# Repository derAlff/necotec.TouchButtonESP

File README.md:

# touchButtonESP
DE: Ein klein wenig Code, zu meinem "Smarter Wandtaster Projekt". EN: A little bit of code, for my "smart wallmounted switch project".

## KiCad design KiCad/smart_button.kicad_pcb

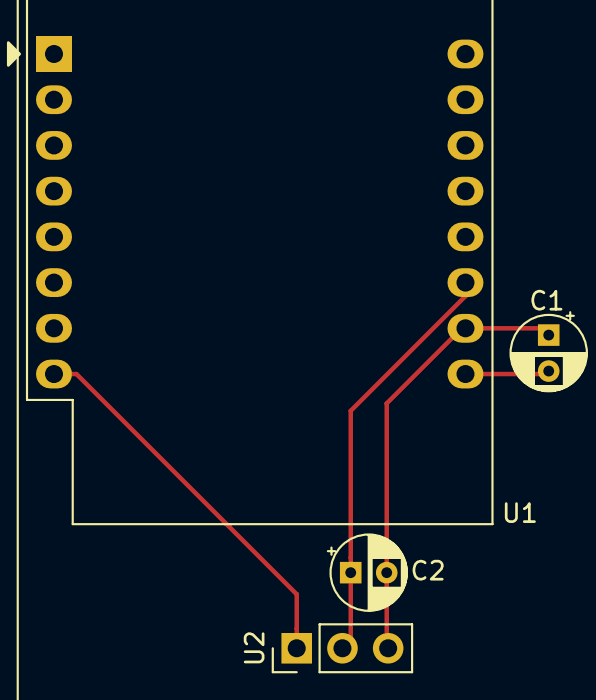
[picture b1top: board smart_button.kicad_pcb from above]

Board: 2 copper layers, 4 parts (0 on the bottom side), 4 nets.

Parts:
C1, C2: 0.1uF; CP_Radial_D4.0mm_P2.00mm
U1: WeMos_D1_mini; WEMOS_D1_mini_light
U2: TOUCH1; PinHeader_1x03_P2.54mm_Vertical

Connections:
GND: C1.1, C2.2, U1.10, U2.3
unnamed: C2.1, U1.11, U2.2
unnamed: U1.8, U2.1
Vin: C1.2, U1.9

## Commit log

2020-05-10 First running version
    First running version. In the KiCad files are the pins for the touch sensor wrong
2020-05-18 Added license
2020-05-22 Foldernames changed
2020-05-22 Deleted old folders
2020-05-30 Ported Arduino project to PlatformIO. Deleted Arduino folder.
2020-05-30 Removed Arduino folder.
2020-05-30 Added pinout picture of Wemos D1 Mini Pro
2020-05-30 Added WiFi connection in Setup.
2020-06-08 Version 1.0 . MQTT is running. Wifi connection is ok. Set hostname an uniqe, because created from MAC-address. At version 1.0 only static MQTT-topics. At the moment work only one topic.
2020-06-08 removed mqtt.h
2020-09-28 Added labels for Merten/Jung Switch
